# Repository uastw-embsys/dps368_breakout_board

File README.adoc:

== DrohnFH DPS368 Breakout Board

This breakout board connects all the pins of the Infineon DPS368 barometric pressure sensor IC to a DIP-8 *W10.16 mm* footprint.

It is pin compatible with the break-off sensor section of the KIT DPS368 2GO board (see https://www.infineon.com/evaluation-board/KIT-DPS368-2GO)

[frame="none",grid="none",cols="^.^4,^.^9,width="100%"]
|====
| image:docs/dps368_breakout.png[] | image:docs/dps368_breakout.jpg[]
|====

WARNING: To keep routing as simple as possible, it does *not* follow the
conventional DIP pin assignment! Please use the connection diagrams below
to connect the breakout board correctly.

WARNING: When replacing a KIT DPS368 2GO sensor, disregard the orientation of the silkscreen
and match the VDD pin of the breakout board (top right corner) to the VDD pin on your target board.
This is due to multiple silkscreen revisions of the KIT DPS368 2GO board with different orientations existing.

The breakout board's pin assignment can be found in its link:datasheet/datasheet.pdf[Datasheet].

For further details see the sensor's datasheet (https://www.infineon.com/assets/row/public/documents/30/49/infineon-dps368-datasheet-en.pdf)

=== Acknowledgement

This work was supported by the City of Vienna via the project 
_Stadt Wien Kompetenzteam für Drohnentechnik in der Fachhochschulausbildung_,
MA23 Projekt Nr. 35-02.

[grid="none",frame="none"]
|====
| image:docs/drohnfh_logo_80.png[] | image:docs/ma23_80.png[] | image:docs/fhtw_80.png[]
|====

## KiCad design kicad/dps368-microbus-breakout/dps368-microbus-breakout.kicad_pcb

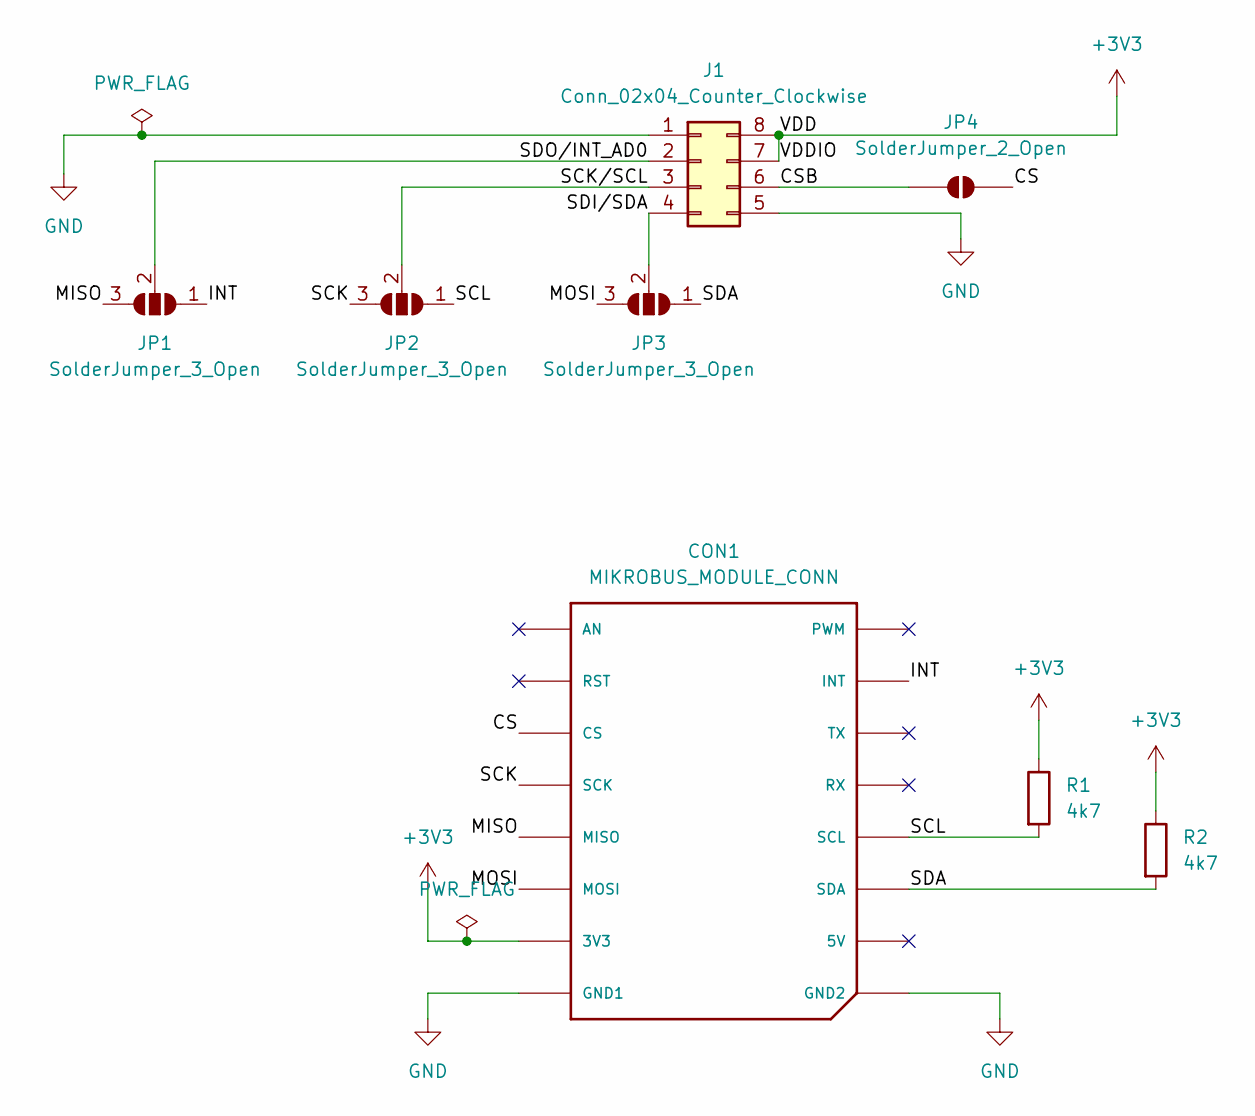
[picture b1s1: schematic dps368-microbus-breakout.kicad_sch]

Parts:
CON1: MIKROBUS_MODULE_CONN
J1: Conn_02x04_Counter_Clockwise; DIP-8_W10.16mm_LongPads
JP1, JP2, JP3: SolderJumper_3_Open; SolderJumper-3_P1.3mm_Open_Pad1.0x1.5mm
JP4: SolderJumper_2_Open; SolderJumper-2_P1.3mm_Open_Pad1.0x1.5mm
R1, R2: 4k7; R_0603_1608Metric

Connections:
+3V3: CON1.P7 (3V3), J1.7, J1.8, R1.1, R2.1
/CS: CON1.P3 (CS), JP4.2 (B)
/CSB: J1.6, JP4.1 (A)
/INT: CON1.P15 (INT), JP1.1 (A)
/MISO: CON1.P5 (MISO), JP1.3 (B)
/MOSI: CON1.P6 (MOSI), JP3.3 (B)
/SCK: CON1.P4 (SCK), JP2.3 (B)
/SCK/SCL: J1.3, JP2.2 (C)
/SCL: CON1.P12 (SCL), JP2.1 (A), R1.2
/SDA: CON1.P11 (SDA), JP3.1 (A), R2.2
/SDI/SDA: J1.4, JP3.2 (C)
/SDO/INT_AD0: J1.2, JP1.2 (C)
GND: CON1.P8 (GND1), CON1.P9 (GND2), J1.1, J1.5

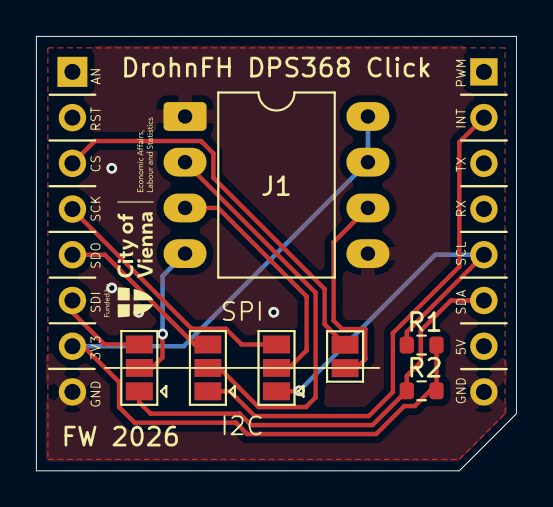
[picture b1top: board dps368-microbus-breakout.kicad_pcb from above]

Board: 2 copper layers, 26.7 x 24.1 mm, 8 parts (0 on the bottom side), 13 nets.

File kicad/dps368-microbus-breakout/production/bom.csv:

Designator,Footprint,Quantity,Value,LCSC Part #
CON1,MIKROBUS_MODULE_CONN,1,MIKROBUS_MODULE_CONN,
J1,DIP-8_W10.16mm_LongPads,1,Conn_02x04_Counter_Clockwise,
"R1, R2",0603,2,4k7,

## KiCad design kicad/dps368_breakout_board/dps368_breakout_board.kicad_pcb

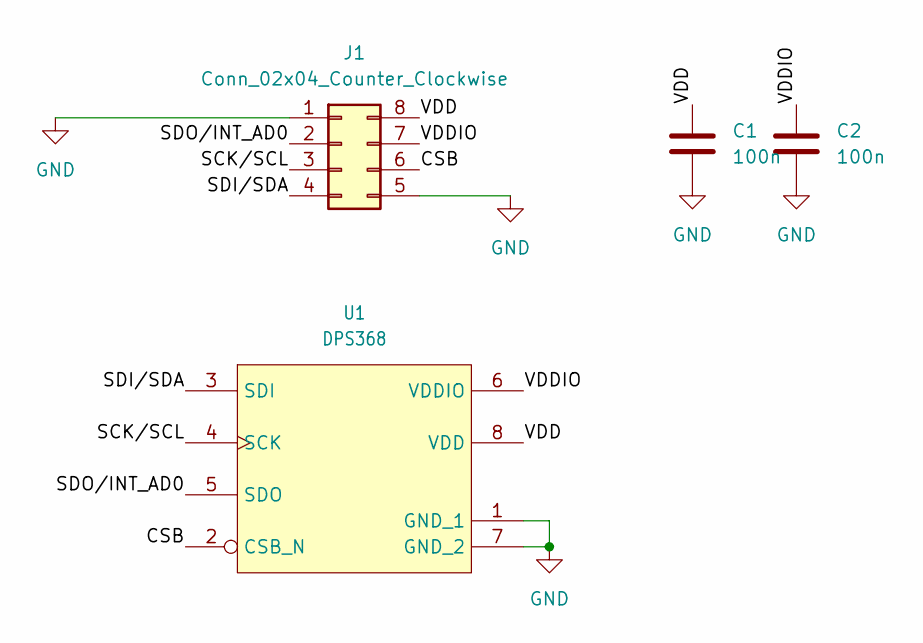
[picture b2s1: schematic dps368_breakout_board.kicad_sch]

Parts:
C1, C2: 100n; C_0603_1608Metric
J1: Conn_02x04_Counter_Clockwise; DIP-8_W10.16mm_LongPads
U1: DPS368; LGA8S145X65P2X4_200X250X110-V

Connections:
/CSB: J1.6, U1.2 (CSB_N)
/SCK/SCL: J1.3, U1.4 (SCK)
/SDI/SDA: J1.4, U1.3 (SDI)
/SDO/INT_AD0: J1.2, U1.5 (SDO)
/VDD: C1.1, J1.8, U1.8 (VDD)
/VDDIO: C2.1, J1.7, U1.6 (VDDIO)
GND: C1.2, C2.2, J1.1, J1.5, U1.1 (GND_1), U1.7 (GND_2)

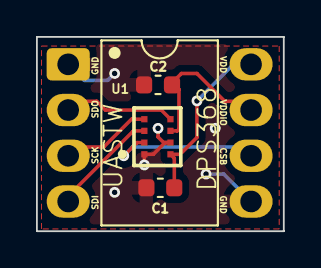
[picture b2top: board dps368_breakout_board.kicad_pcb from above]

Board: 2 copper layers, 13.7 x 10.8 mm, 4 parts (0 on the bottom side), 7 nets.
